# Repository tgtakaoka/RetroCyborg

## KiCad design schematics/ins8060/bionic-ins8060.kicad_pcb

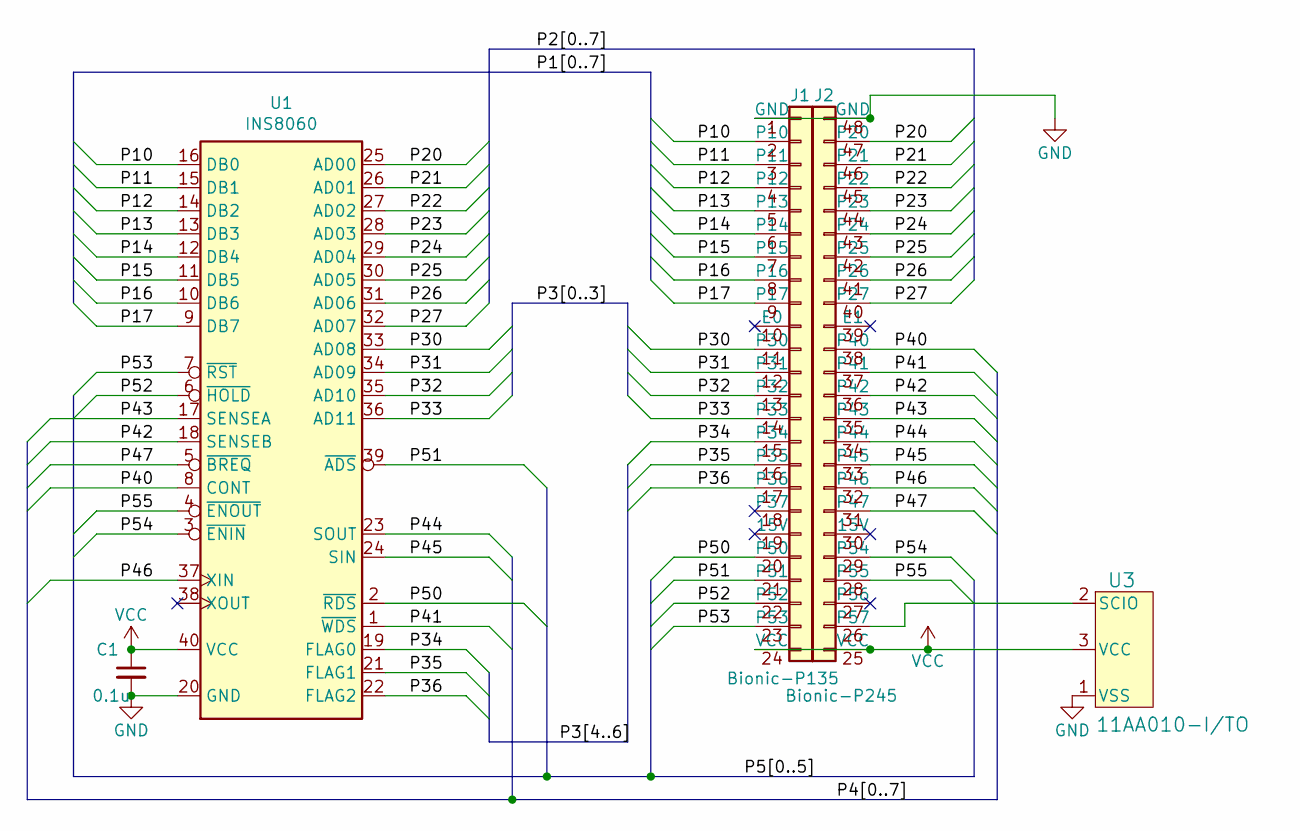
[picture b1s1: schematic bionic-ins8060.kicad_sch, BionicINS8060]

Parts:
C1: 0.1u; C_Disc_D3.4mm_W2.1mm_P2.50mm
J1: Bionic-P135; Bionic-P135_Vertical
J2: Bionic-P245; Bionic-P245_Vertical
U1: INS8060; DIP-40_W15.24mm
U3: 11AA010-I/TO; TO-92_MC_MCH

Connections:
/P10: J1.2 (P10), U1.16 (DB0)
/P11: J1.3 (P11), U1.15 (DB1)
/P12: J1.4 (P12), U1.14 (DB2)
/P13: J1.5 (P13), U1.13 (DB3)
/P14: J1.6 (P14), U1.12 (DB4)
/P15: J1.7 (P15), U1.11 (DB5)
/P16: J1.8 (P16), U1.10 (DB6)
/P17: J1.9 (P17), U1.9 (DB7)
/P20: J2.47 (P20), U1.25 (AD00)
/P21: J2.46 (P21), U1.26 (AD01)
/P22: J2.45 (P22), U1.27 (AD02)
/P23: J2.44 (P23), U1.28 (AD03)
/P24: J2.43 (P24), U1.29 (AD04)
/P25: J2.42 (P25), U1.30 (AD05)
/P26: J2.41 (P26), U1.31 (AD06)
/P27: J2.40 (P27), U1.32 (AD07)
/P30: J1.11 (P30), U1.33 (AD08)
/P31: J1.12 (P31), U1.34 (AD09)
/P32: J1.13 (P32), U1.35 (AD10)
/P33: J1.14 (P33), U1.36 (AD11)
/P34: J1.15 (P34), U1.19 (FLAG0)
/P35: J1.16 (P35), U1.21 (FLAG1)
/P36: J1.17 (P36), U1.22 (FLAG2)
/P40: J2.38 (P40), U1.8 (CONT)
/P41: J2.37 (P41), U1.1 (~WDS)
/P42: J2.36 (P42), U1.18 (SENSEB)
/P43: J2.35 (P43), U1.17 (SENSEA)
/P44: J2.34 (P44), U1.23 (SOUT)
/P45: J2.33 (P45), U1.24 (SIN)
/P46: J2.32 (P46), U1.37 (XIN)
/P47: J2.31 (P47), U1.5 (~BREQ)
/P50: J1.20 (P50), U1.2 (~RDS)
/P51: J1.21 (P51), U1.39 (~ADS)
/P52: J1.22 (P52), U1.6 (~HOLD)
/P53: J1.23 (P53), U1.7 (~RST)
/P54: J2.29 (P54), U1.3 (~ENIN)
/P55: J2.28 (P55), U1.4 (~ENOUT)
GND: C1.2, J1.1 (GND), J2.48 (GND), U1.20 (GND), U3.1 (VSS)
unnamed: J2.26 (P57), U3.2 (SCIO)
VCC: C1.1, J1.24 (VCC), J2.25 (VCC), U1.40 (VCC), U3.3 (VCC)

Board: 2 copper layers, 9 parts (0 on the bottom side), 40 nets, no tracks yet.

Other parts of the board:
MH1, MH2, MH3, MH4: MountingHole_3.2mm_M3

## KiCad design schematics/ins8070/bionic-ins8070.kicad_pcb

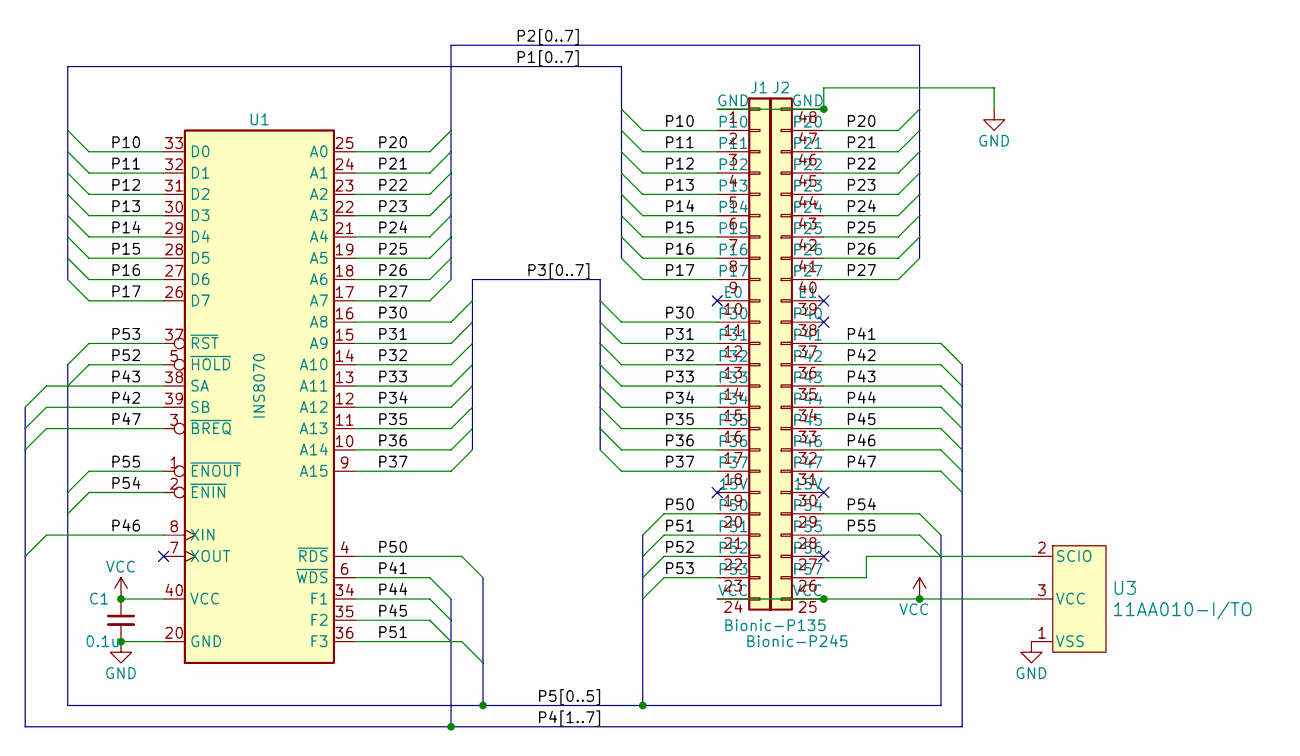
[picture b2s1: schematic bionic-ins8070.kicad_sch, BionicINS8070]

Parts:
C1: 0.1u; C_Disc_D3.4mm_W2.1mm_P2.50mm
J1: Bionic-P135; Bionic-P135_Vertical
J2: Bionic-P245; Bionic-P245_Vertical
U1: INS8070; DIP-40_W15.24mm
U3: 11AA010-I/TO; TO-92_MC_MCH

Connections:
/P10: J1.2 (P10), U1.33 (D0)
/P11: J1.3 (P11), U1.32 (D1)
/P12: J1.4 (P12), U1.31 (D2)
/P13: J1.5 (P13), U1.30 (D3)
/P14: J1.6 (P14), U1.29 (D4)
/P15: J1.7 (P15), U1.28 (D5)
/P16: J1.8 (P16), U1.27 (D6)
/P17: J1.9 (P17), U1.26 (D7)
/P20: J2.47 (P20), U1.25 (A0)
/P21: J2.46 (P21), U1.24 (A1)
/P22: J2.45 (P22), U1.23 (A2)
/P23: J2.44 (P23), U1.22 (A3)
/P24: J2.43 (P24), U1.21 (A4)
/P25: J2.42 (P25), U1.19 (A5)
/P26: J2.41 (P26), U1.18 (A6)
/P27: J2.40 (P27), U1.17 (A7)
/P30: J1.11 (P30), U1.16 (A8)
/P31: J1.12 (P31), U1.15 (A9)
/P32: J1.13 (P32), U1.14 (A10)
/P33: J1.14 (P33), U1.13 (A11)
/P34: J1.15 (P34), U1.12 (A12)
/P35: J1.16 (P35), U1.11 (A13)
/P36: J1.17 (P36), U1.10 (A14)
/P37: J1.18 (P37), U1.9 (A15)
/P41: J2.37 (P41), U1.6 (~WDS)
/P42: J2.36 (P42), U1.39 (SB)
/P43: J2.35 (P43), U1.38 (SA)
/P44: J2.34 (P44), U1.34 (F1)
/P45: J2.33 (P45), U1.35 (F2)
/P46: J2.32 (P46), U1.8 (XIN)
/P47: J2.31 (P47), U1.3 (~BREQ)
/P50: J1.20 (P50), U1.4 (~RDS)
/P51: J1.21 (P51), U1.36 (F3)
/P52: J1.22 (P52), U1.5 (~HOLD)
/P53: J1.23 (P53), U1.37 (~RST)
/P54: J2.29 (P54), U1.2 (~ENIN)
/P55: J2.28 (P55), U1.1 (~ENOUT)
GND: C1.2, J1.1 (GND), J2.48 (GND), U1.20 (GND), U3.1 (VSS)
unnamed: J2.26 (P57), U3.2 (SCIO)
VCC: C1.1, J1.24 (VCC), J2.25 (VCC), U1.40 (VCC), U3.3 (VCC)

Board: 2 copper layers, 9 parts (0 on the bottom side), 40 nets, no tracks yet.

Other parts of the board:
MH1, MH2, MH3, MH4: MountingHole_3.2mm_M3

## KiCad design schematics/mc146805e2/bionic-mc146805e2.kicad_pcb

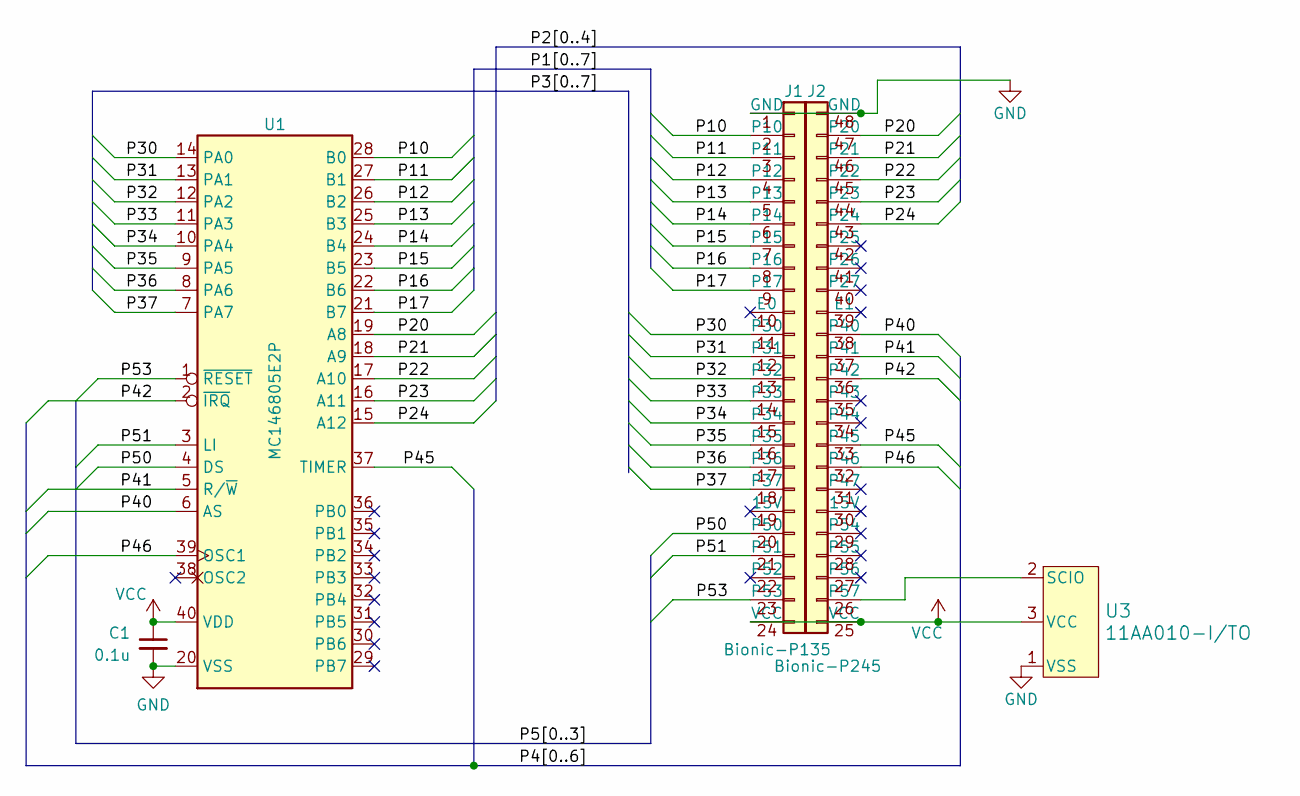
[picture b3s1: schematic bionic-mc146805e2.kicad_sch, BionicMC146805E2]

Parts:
C1: 0.1u; C_Disc_D3.4mm_W2.1mm_P2.50mm
J1: Bionic-P135; Bionic-P135_Vertical
J2: Bionic-P245; Bionic-P245_Vertical
U1: MC146805E2P; DIP-40_W15.24mm
U3: 11AA010-I/TO; TO-92_MC_MCH

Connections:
/P10: J1.2 (P10), U1.28 (B0)
/P11: J1.3 (P11), U1.27 (B1)
/P12: J1.4 (P12), U1.26 (B2)
/P13: J1.5 (P13), U1.25 (B3)
/P14: J1.6 (P14), U1.24 (B4)
/P15: J1.7 (P15), U1.23 (B5)
/P16: J1.8 (P16), U1.22 (B6)
/P17: J1.9 (P17), U1.21 (B7)
/P20: J2.47 (P20), U1.19 (A8)
/P21: J2.46 (P21), U1.18 (A9)
/P22: J2.45 (P22), U1.17 (A10)
/P23: J2.44 (P23), U1.16 (A11)
/P24: J2.43 (P24), U1.15 (A12)
/P30: J1.11 (P30), U1.14 (PA0)
/P31: J1.12 (P31), U1.13 (PA1)
/P32: J1.13 (P32), U1.12 (PA2)
/P33: J1.14 (P33), U1.11 (PA3)
/P34: J1.15 (P34), U1.10 (PA4)
/P35: J1.16 (P35), U1.9 (PA5)
/P36: J1.17 (P36), U1.8 (PA6)
/P37: J1.18 (P37), U1.7 (PA7)
/P40: J2.38 (P40), U1.6 (AS)
/P41: J2.37 (P41), U1.5 (R/~W)
/P42: J2.36 (P42), U1.2 (~IRQ)
/P45: J2.33 (P45), U1.37 (TIMER)
/P46: J2.32 (P46), U1.39 (OSC1)
/P50: J1.20 (P50), U1.4 (DS)
/P51: J1.21 (P51), U1.3 (LI)
/P53: J1.23 (P53), U1.1 (~RESET)
GND: C1.2, J1.1 (GND), J2.48 (GND), U1.20 (VSS), U3.1 (VSS)
unnamed: J2.26 (P57), U3.2 (SCIO)
VCC: C1.1, J1.24 (VCC), J2.25 (VCC), U1.40 (VDD), U3.3 (VCC)

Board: 2 copper layers, 9 parts (0 on the bottom side), 32 nets, no tracks yet.

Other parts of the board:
MH1, MH2, MH3, MH4: MountingHole_3.2mm_M3

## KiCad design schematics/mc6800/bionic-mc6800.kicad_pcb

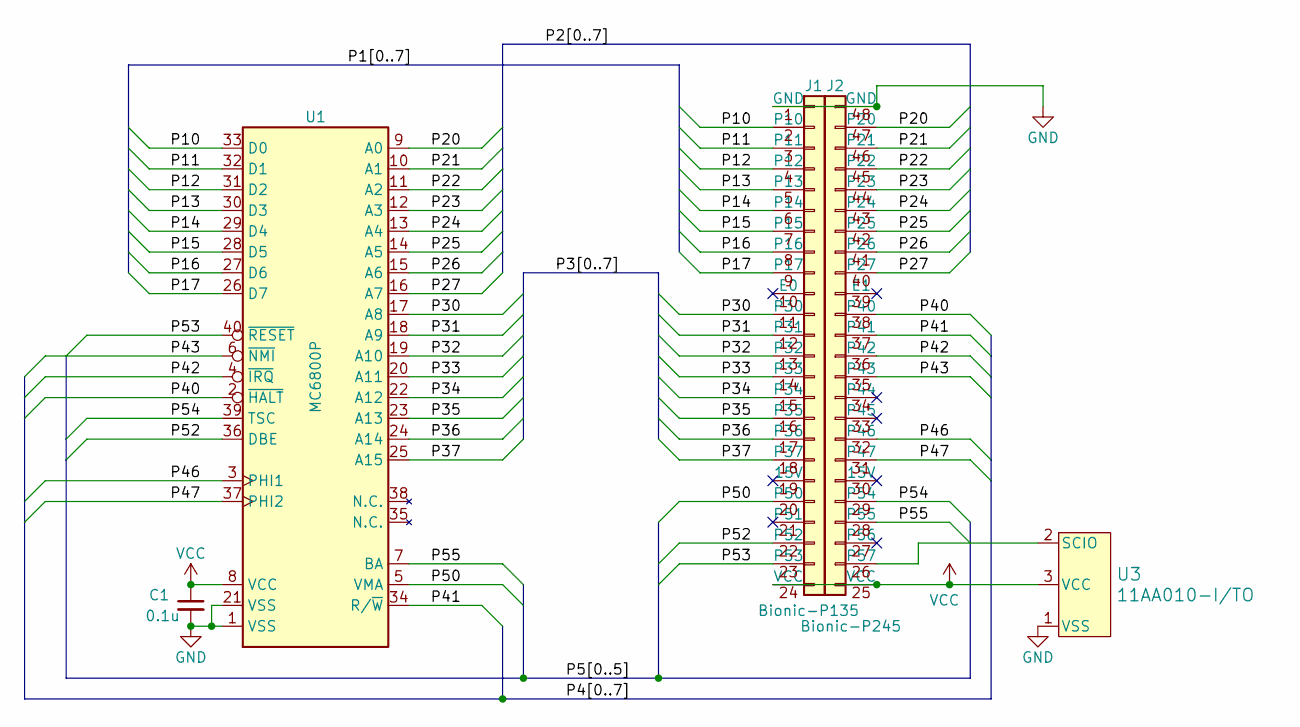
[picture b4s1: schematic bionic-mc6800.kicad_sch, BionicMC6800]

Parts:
C1: 0.1u; C_Disc_D3.4mm_W2.1mm_P2.50mm
J1: Bionic-P135; Bionic-P135_Vertical
J2: Bionic-P245; Bionic-P245_Vertical
U1: MC6800P; DIP-40_W15.24mm
U3: 11AA010-I/TO; TO-92_MC_MCH

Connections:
/P10: J1.2 (P10), U1.33 (D0)
/P11: J1.3 (P11), U1.32 (D1)
/P12: J1.4 (P12), U1.31 (D2)
/P13: J1.5 (P13), U1.30 (D3)
/P14: J1.6 (P14), U1.29 (D4)
/P15: J1.7 (P15), U1.28 (D5)
/P16: J1.8 (P16), U1.27 (D6)
/P17: J1.9 (P17), U1.26 (D7)
/P20: J2.47 (P20), U1.9 (A0)
/P21: J2.46 (P21), U1.10 (A1)
/P22: J2.45 (P22), U1.11 (A2)
/P23: J2.44 (P23), U1.12 (A3)
/P24: J2.43 (P24), U1.13 (A4)
/P25: J2.42 (P25), U1.14 (A5)
/P26: J2.41 (P26), U1.15 (A6)
/P27: J2.40 (P27), U1.16 (A7)
/P30: J1.11 (P30), U1.17 (A8)
/P31: J1.12 (P31), U1.18 (A9)
/P32: J1.13 (P32), U1.19 (A10)
/P33: J1.14 (P33), U1.20 (A11)
/P34: J1.15 (P34), U1.22 (A12)
/P35: J1.16 (P35), U1.23 (A13)
/P36: J1.17 (P36), U1.24 (A14)
/P37: J1.18 (P37), U1.25 (A15)
/P40: J2.38 (P40), U1.2 (~HALT)
/P41: J2.37 (P41), U1.34 (R/~W)
/P42: J2.36 (P42), U1.4 (~IRQ)
/P43: J2.35 (P43), U1.6 (~NMI)
/P46: J2.32 (P46), U1.3 (PHI1)
/P47: J2.31 (P47), U1.37 (PHI2)
/P50: J1.20 (P50), U1.5 (VMA)
/P52: J1.22 (P52), U1.36 (DBE)
/P53: J1.23 (P53), U1.40 (~RESET)
/P54: J2.29 (P54), U1.39 (TSC)
/P55: J2.28 (P55), U1.7 (BA)
GND: C1.2, J1.1 (GND), J2.48 (GND), U1.1 (VSS), U1.21 (VSS), U3.1 (VSS)
unnamed: J2.26 (P57), U3.2 (SCIO)
VCC: C1.1, J1.24 (VCC), J2.25 (VCC), U1.8 (VCC), U3.3 (VCC)

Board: 2 copper layers, 9 parts (0 on the bottom side), 38 nets, no tracks yet.

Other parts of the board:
MH1, MH2, MH3, MH4: MountingHole_3.2mm_M3

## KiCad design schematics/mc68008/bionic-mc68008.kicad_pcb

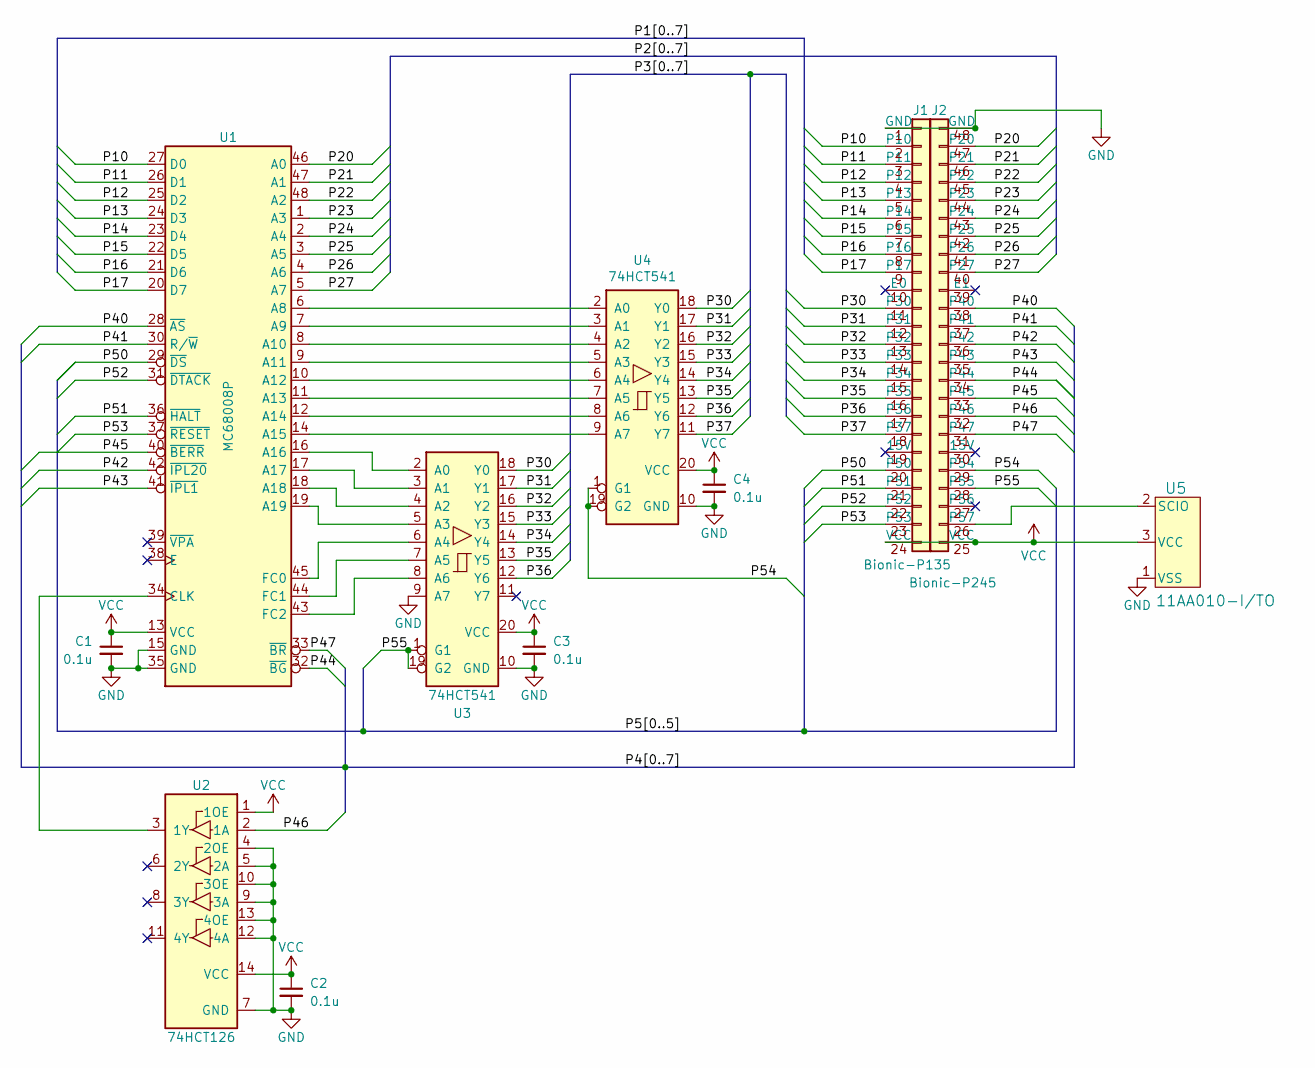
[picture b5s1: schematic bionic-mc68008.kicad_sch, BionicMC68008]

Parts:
C1, C2, C3, C4: 0.1u; C_Disc_D3.4mm_W2.1mm_P2.50mm
J1: Bionic-P135; Bionic-P135_Vertical
J2: Bionic-P245; Bionic-P245_Vertical
U1: MC68008P; DIP-48_W15.24mm
U2: 74HCT126; DIP-14_W7.62mm
U3, U4: 74HCT541; DIP-20_W7.62mm
U5: 11AA010-I/TO; TO-92_MC_MCH

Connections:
/P10: J1.2 (P10), U1.27 (D0); also elsewhere on the board
/P11: J1.3 (P11), U1.26 (D1); also elsewhere on the board
/P12: J1.4 (P12), U1.25 (D2); also elsewhere on the board
/P13: J1.5 (P13), U1.24 (D3); also elsewhere on the board
/P14: J1.6 (P14), U1.23 (D4); also elsewhere on the board
/P15: J1.7 (P15), U1.22 (D5); also elsewhere on the board
/P16: J1.8 (P16), U1.21 (D6); also elsewhere on the board
/P17: J1.9 (P17), U1.20 (D7); also elsewhere on the board
/P20: J1.47 (P20), J2.47 (P20), U1.46 (A0)
/P21: J1.46 (P21), J2.46 (P21), U1.47 (A1)
/P22: J1.45 (P22), J2.45 (P22), U1.48 (A2)
/P23: J1.44 (P23), J2.44 (P23), U1.1 (A3)
/P24: J1.43 (P24), J2.43 (P24), U1.2 (A4)
/P25: J1.42 (P25), J2.42 (P25), U1.3 (A5)
/P26: J1.41 (P26), J2.41 (P26), U1.4 (A6)
/P27: J1.40 (P27), J2.40 (P27), U1.5 (A7)
/P30: J1.11 (P30), U3.18 (Y0), U4.18 (Y0); also elsewhere on the board
/P31: J1.12 (P31), U3.17 (Y1), U4.17 (Y1); also elsewhere on the board
/P32: J1.13 (P32), U3.16 (Y2), U4.16 (Y2); also elsewhere on the board
/P33: J1.14 (P33), U3.15 (Y3), U4.15 (Y3); also elsewhere on the board
/P34: J1.15 (P34), U3.14 (Y4), U4.14 (Y4); also elsewhere on the board
/P35: J1.16 (P35), U3.13 (Y5), U4.13 (Y5); also elsewhere on the board
/P36: J1.17 (P36), U3.12 (Y6), U4.12 (Y6); also elsewhere on the board
/P37: J1.18 (P37), U4.11 (Y7); also elsewhere on the board
/P40: J1.38 (P40), J2.38 (P40), U1.28 (~AS)
/P41: J1.37 (P41), J2.37 (P41), U1.30 (R/~W)
/P42: J1.36 (P42), J2.36 (P42), U1.42 (~IPL20)
/P43: J1.35 (P43), J2.35 (P43), U1.41 (~IPL1)
/P44: J1.34 (P44), J2.34 (P44), U1.32 (~BG)
/P45: J1.33 (P45), J2.33 (P45), U1.40 (~BERR)
/P46: J1.32 (P46), J2.32 (P46), U2.2 (1A)
/P47: J1.31 (P47), J2.31 (P47), U1.33 (~BR)
/P50: J1.20 (P50), U1.29 (~DS); also elsewhere on the board
/P51: J1.21 (P51), U1.36 (~HALT); also elsewhere on the board
/P52: J1.22 (P52), U1.31 (~DTACK); also elsewhere on the board
/P53: J1.23 (P53), U1.37 (~RESET); also elsewhere on the board
/P54: J1.29 (P54), J2.29 (P54), U4.1 (G1), U4.19 (G2)
/P55: J1.28 (P55), J2.28 (P55), U3.1 (G1), U3.19 (G2)
GND: C1.2, C2.2, C3.2, C4.2, J1.1 (GND), J1.48 (GND), J2.48 (GND), U1.15 (GND), U1.35 (GND), U2.4 (2OE), U2.5 (2A), U2.7 (GND), U2.9 (3A), U2.10 (3OE), U2.12 (4A), U2.13 (4OE), U3.9 (A7), U3.10 (GND), U4.10 (GND), U5.1 (VSS); also elsewhere on the board
unnamed: J2.26 (P57), U5.2 (SCIO)
unnamed: U1.6 (A8), U4.2 (A0)
unnamed: U1.7 (A9), U4.3 (A1)
unnamed: U1.8 (A10), U4.4 (A2)
unnamed: U1.9 (A11), U4.5 (A3)
unnamed: U1.10 (A12), U4.6 (A4)
unnamed: U1.11 (A13), U4.7 (A5)
unnamed: U1.12 (A14), U4.8 (A6)
unnamed: U1.14 (A15), U4.9 (A7)
unnamed: U1.16 (A16), U3.2 (A0)
unnamed: U1.17 (A17), U3.3 (A1)
unnamed: U1.18 (A18), U3.4 (A2)
unnamed: U1.19 (A19), U3.5 (A3)
unnamed: U1.34 (CLK), U2.3 (1Y)
unnamed: U1.45 (FC0), U3.6 (A4)
unnamed: U1.44 (FC1), U3.7 (A5)
unnamed: U1.43 (FC2), U3.8 (A6)
VCC: C1.1, C2.1, C3.1, C4.1, J1.24 (VCC), J1.25 (VCC), J2.25 (VCC), U1.13 (VCC), U2.1 (1OE), U2.14 (VCC), U3.20 (VCC), U4.20 (VCC), U5.3 (VCC); also elsewhere on the board

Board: 2 copper layers, 16 parts (0 on the bottom side), 57 nets, no tracks yet.

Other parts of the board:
J1#2: Bionic-P135; Bionic-P135_Vertical
MH1, MH2, MH3, MH4: MountingHole_3.2mm_M3

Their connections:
/P10: J1#2.2 (P10); also elsewhere on the board
/P11: J1#2.3 (P11); also elsewhere on the board
/P12: J1#2.4 (P12); also elsewhere on the board
/P13: J1#2.5 (P13); also elsewhere on the board
/P14: J1#2.6 (P14); also elsewhere on the board
/P15: J1#2.7 (P15); also elsewhere on the board
/P16: J1#2.8 (P16); also elsewhere on the board
/P17: J1#2.9 (P17); also elsewhere on the board
/P30: J1#2.11 (P30); also elsewhere on the board
/P31: J1#2.12 (P31); also elsewhere on the board
/P32: J1#2.13 (P32); also elsewhere on the board
/P33: J1#2.14 (P33); also elsewhere on the board
/P34: J1#2.15 (P34); also elsewhere on the board
/P35: J1#2.16 (P35); also elsewhere on the board
/P36: J1#2.17 (P36); also elsewhere on the board
/P37: J1#2.18 (P37); also elsewhere on the board
/P50: J1#2.20 (P50); also elsewhere on the board
/P51: J1#2.21 (P51); also elsewhere on the board
/P52: J1#2.22 (P52); also elsewhere on the board
/P53: J1#2.23 (P53); also elsewhere on the board
GND: J1#2.1 (GND); also elsewhere on the board
VCC: J1#2.24 (VCC); also elsewhere on the board

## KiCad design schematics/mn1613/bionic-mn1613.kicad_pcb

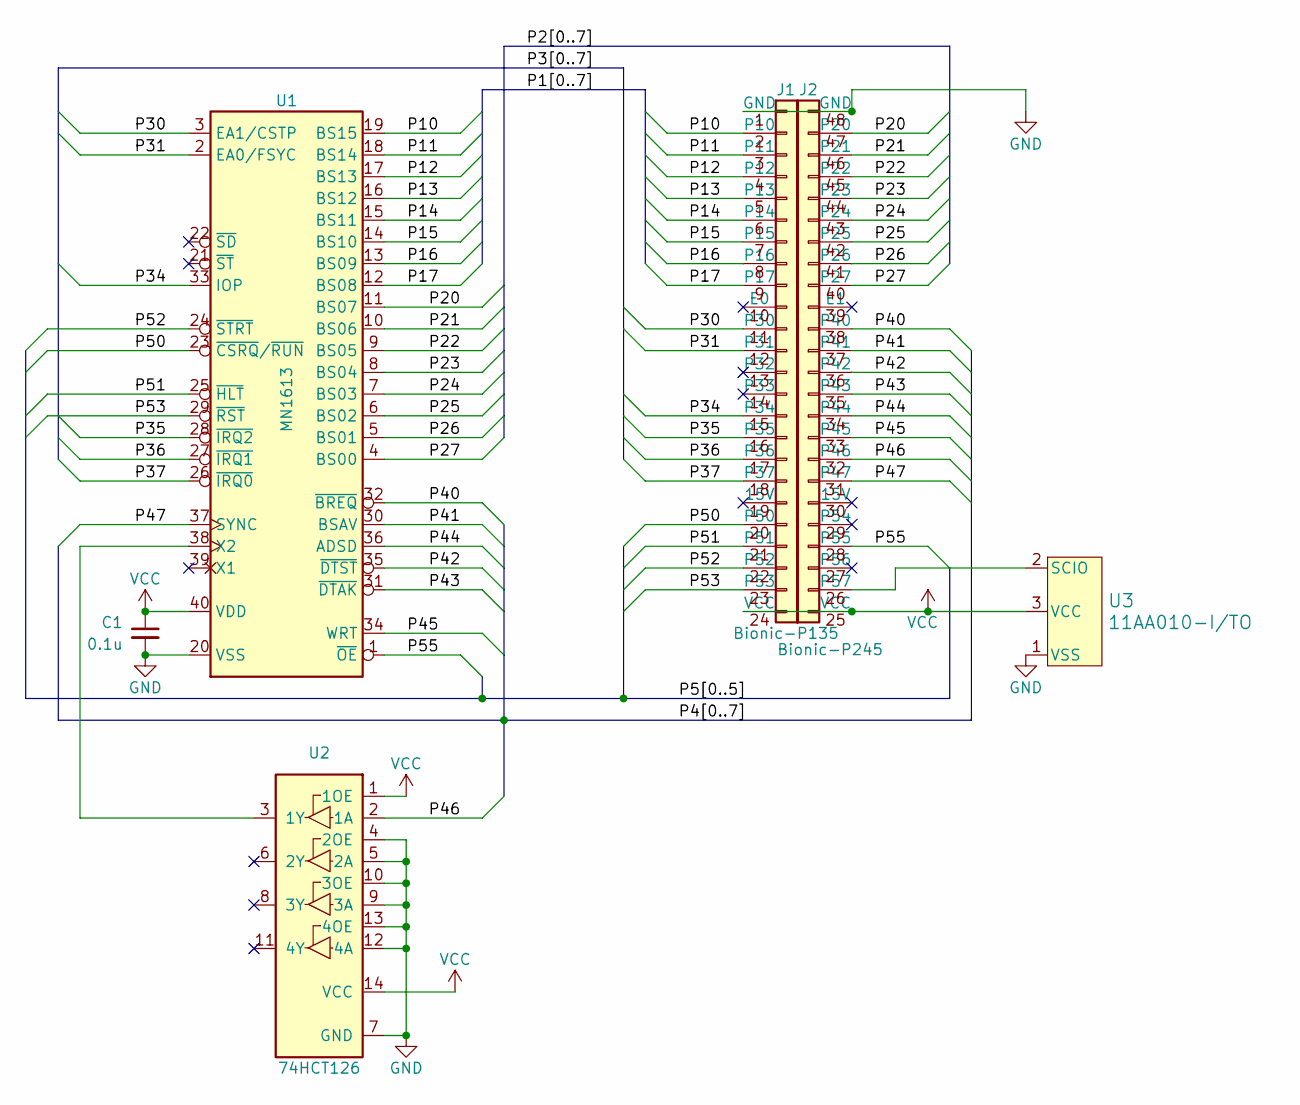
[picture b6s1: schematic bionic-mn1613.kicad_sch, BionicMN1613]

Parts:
C1: 0.1u; C_Disc_D3.4mm_W2.1mm_P2.50mm
J1: Bionic-P135; Bionic-P135_Vertical
J2: Bionic-P245; Bionic-P245_Vertical
U1: MN1613; DIP-40_W15.24mm
U2: 74HCT126; DIP-14_W7.62mm
U3: 11AA010-I/TO; TO-92_MC_MCH

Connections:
/P10: J1.2 (P10), U1.19 (BS15)
/P11: J1.3 (P11), U1.18 (BS14)
/P12: J1.4 (P12), U1.17 (BS13)
/P13: J1.5 (P13), U1.16 (BS12)
/P14: J1.6 (P14), U1.15 (BS11)
/P15: J1.7 (P15), U1.14 (BS10)
/P16: J1.8 (P16), U1.13 (BS09)
/P17: J1.9 (P17), U1.12 (BS08)
/P20: J2.47 (P20), U1.11 (BS07)
/P21: J2.46 (P21), U1.10 (BS06)
/P22: J2.45 (P22), U1.9 (BS05)
/P23: J2.44 (P23), U1.8 (BS04)
/P24: J2.43 (P24), U1.7 (BS03)
/P25: J2.42 (P25), U1.6 (BS02)
/P26: J2.41 (P26), U1.5 (BS01)
/P27: J2.40 (P27), U1.4 (BS00)
/P30: J1.11 (P30), U1.3 (EA1/CSTP)
/P31: J1.12 (P31), U1.2 (EA0/FSYC)
/P34: J1.15 (P34), U1.33 (IOP)
/P35: J1.16 (P35), U1.28 (~IRQ2)
/P36: J1.17 (P36), U1.27 (~IRQ1)
/P37: J1.18 (P37), U1.26 (~IRQ0)
/P40: J2.38 (P40), U1.32 (~BREQ)
/P41: J2.37 (P41), U1.30 (BSAV)
/P42: J2.36 (P42), U1.35 (~DTST)
/P43: J2.35 (P43), U1.31 (~DTAK)
/P44: J2.34 (P44), U1.36 (ADSD)
/P45: J2.33 (P45), U1.34 (WRT)
/P46: J2.32 (P46), U2.2 (1A)
/P47: J2.31 (P47), U1.37 (SYNC)
/P50: J1.20 (P50), U1.23 (~CSRQ/~RUN)
/P51: J1.21 (P51), U1.25 (~HLT)
/P52: J1.22 (P52), U1.24 (~STRT)
/P53: J1.23 (P53), U1.29 (~RST)
/P55: J2.28 (P55), U1.1 (~OE)
GND: C1.2, J1.1 (GND), J2.48 (GND), U1.20 (VSS), U2.4 (2OE), U2.5 (2A), U2.7 (GND), U2.9 (3A), U2.10 (3OE), U2.12 (4A), U2.13 (4OE), U3.1 (VSS)
unnamed: J2.26 (P57), U3.2 (SCIO)
unnamed: U1.38 (X2), U2.3 (1Y)
VCC: C1.1, J1.24 (VCC), J2.25 (VCC), U1.40 (VDD), U2.1 (1OE), U2.14 (VCC), U3.3 (VCC)

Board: 2 copper layers, 10 parts (0 on the bottom side), 39 nets, no tracks yet.

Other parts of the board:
MH1, MH2, MH3, MH4: MountingHole_3.2mm_M3

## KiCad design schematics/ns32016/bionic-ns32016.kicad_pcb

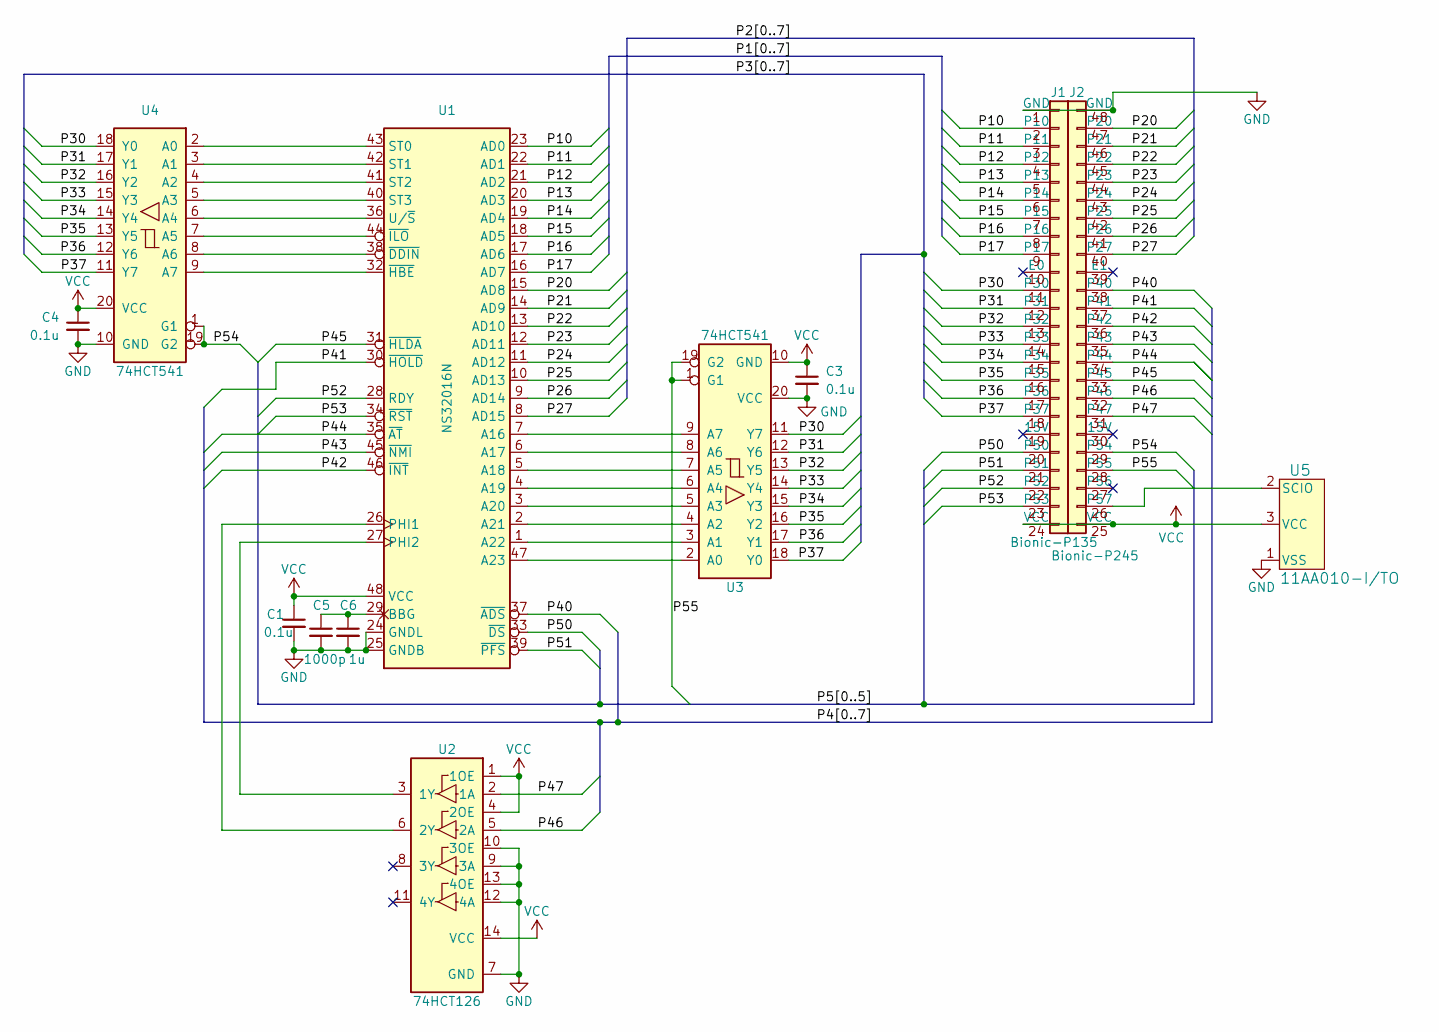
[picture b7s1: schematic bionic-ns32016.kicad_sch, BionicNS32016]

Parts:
C1, C3, C4: 0.1u; C_Disc_D3.4mm_W2.1mm_P2.50mm
C5: 1000p; C_Disc_D3.4mm_W2.1mm_P2.50mm
C6: 1u; C_Disc_D3.4mm_W2.1mm_P2.50mm
J1: Bionic-P135; Bionic-P135_Vertical
J2: Bionic-P245; Bionic-P245_Vertical
U1: NS32016N; DIP-48_W15.24mm
U2: 74HCT126; DIP-14_W7.62mm
U3, U4: 74HCT541; DIP-20_W7.62mm
U5: 11AA010-I/TO; TO-92_MC_MCH

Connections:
/P10: J1.2 (P10), U1.23 (AD0)
/P11: J1.3 (P11), U1.22 (AD1)
/P12: J1.4 (P12), U1.21 (AD2)
/P13: J1.5 (P13), U1.20 (AD3)
/P14: J1.6 (P14), U1.19 (AD4)
/P15: J1.7 (P15), U1.18 (AD5)
/P16: J1.8 (P16), U1.17 (AD6)
/P17: J1.9 (P17), U1.16 (AD7)
/P20: J2.47 (P20), U1.15 (AD8)
/P21: J2.46 (P21), U1.14 (AD9)
/P22: J2.45 (P22), U1.13 (AD10)
/P23: J2.44 (P23), U1.12 (AD11)
/P24: J2.43 (P24), U1.11 (AD12)
/P25: J2.42 (P25), U1.10 (AD13)
/P26: J2.41 (P26), U1.9 (AD14)
/P27: J2.40 (P27), U1.8 (AD15)
/P30: J1.11 (P30), U3.11 (Y7), U4.18 (Y0)
/P31: J1.12 (P31), U3.12 (Y6), U4.17 (Y1)
/P32: J1.13 (P32), U3.13 (Y5), U4.16 (Y2)
/P33: J1.14 (P33), U3.14 (Y4), U4.15 (Y3)
/P34: J1.15 (P34), U3.15 (Y3), U4.14 (Y4)
/P35: J1.16 (P35), U3.16 (Y2), U4.13 (Y5)
/P36: J1.17 (P36), U3.17 (Y1), U4.12 (Y6)
/P37: J1.18 (P37), U3.18 (Y0), U4.11 (Y7)
/P40: J2.38 (P40), U1.37 (~ADS)
/P41: J2.37 (P41), U1.30 (~HOLD)
/P42: J2.36 (P42), U1.46 (~INT)
/P43: J2.35 (P43), U1.45 (~NMI)
/P44: J2.34 (P44), U1.35 (~AT)
/P45: J2.33 (P45), U1.31 (~HLDA)
/P46: J2.32 (P46), U2.5 (2A)
/P47: J2.31 (P47), U2.2 (1A)
/P50: J1.20 (P50), U1.33 (~DS)
/P51: J1.21 (P51), U1.39 (~PFS)
/P52: J1.22 (P52), U1.28 (RDY)
/P53: J1.23 (P53), U1.34 (~RST)
/P54: J2.29 (P54), U4.1 (G1), U4.19 (G2)
/P55: J2.28 (P55), U3.1 (G1), U3.19 (G2)
GND: C1.2, C3.2, C4.2, C5.2, C6.2, J1.1 (GND), J2.48 (GND), U1.24 (GNDL), U1.25 (GNDB), U2.7 (GND), U2.9 (3A), U2.10 (3OE), U2.12 (4A), U2.13 (4OE), U3.20 (VCC), U4.10 (GND), U5.1 (VSS); also elsewhere on the board
unnamed: J2.26 (P57), U5.2 (SCIO)
unnamed: U1.7 (A16), U3.9 (A7)
unnamed: U1.6 (A17), U3.8 (A6)
unnamed: U1.5 (A18), U3.7 (A5)
unnamed: U1.4 (A19), U3.6 (A4)
unnamed: U1.3 (A20), U3.5 (A3)
unnamed: U1.2 (A21), U3.4 (A2)
unnamed: U1.1 (A22), U3.3 (A1)
unnamed: U1.47 (A23), U3.2 (A0)
unnamed: C5.1, C6.1, U1.29 (BBG)
unnamed: U1.26 (PHI1), U2.6 (2Y)
unnamed: U1.27 (PHI2), U2.3 (1Y)
unnamed: U1.43 (ST0), U4.2 (A0)
unnamed: U1.42 (ST1), U4.3 (A1)
unnamed: U1.41 (ST2), U4.4 (A2)
unnamed: U1.40 (ST3), U4.5 (A3)
unnamed: U1.36 (U/~S), U4.6 (A4)
unnamed: U1.38 (~DDIN), U4.8 (A6)
unnamed: U1.32 (~HBE), U4.9 (A7)
unnamed: U1.44 (~ILO), U4.7 (A5)
VCC: C1.1, C3.1, C4.1, J1.24 (VCC), J2.25 (VCC), U1.48 (VCC), U2.1 (1OE), U2.4 (2OE), U2.14 (VCC), U3.10 (GND), U4.20 (VCC), U5.3 (VCC); also elsewhere on the board

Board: 2 copper layers, 17 parts (0 on the bottom side), 60 nets, no tracks yet.

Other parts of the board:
C2: 0.1u; C_Disc_D3.4mm_W2.1mm_P2.50mm
MH1, MH2, MH3, MH4: MountingHole_3.2mm_M3

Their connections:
GND: C2.2; also elsewhere on the board
VCC: C2.1; also elsewhere on the board
